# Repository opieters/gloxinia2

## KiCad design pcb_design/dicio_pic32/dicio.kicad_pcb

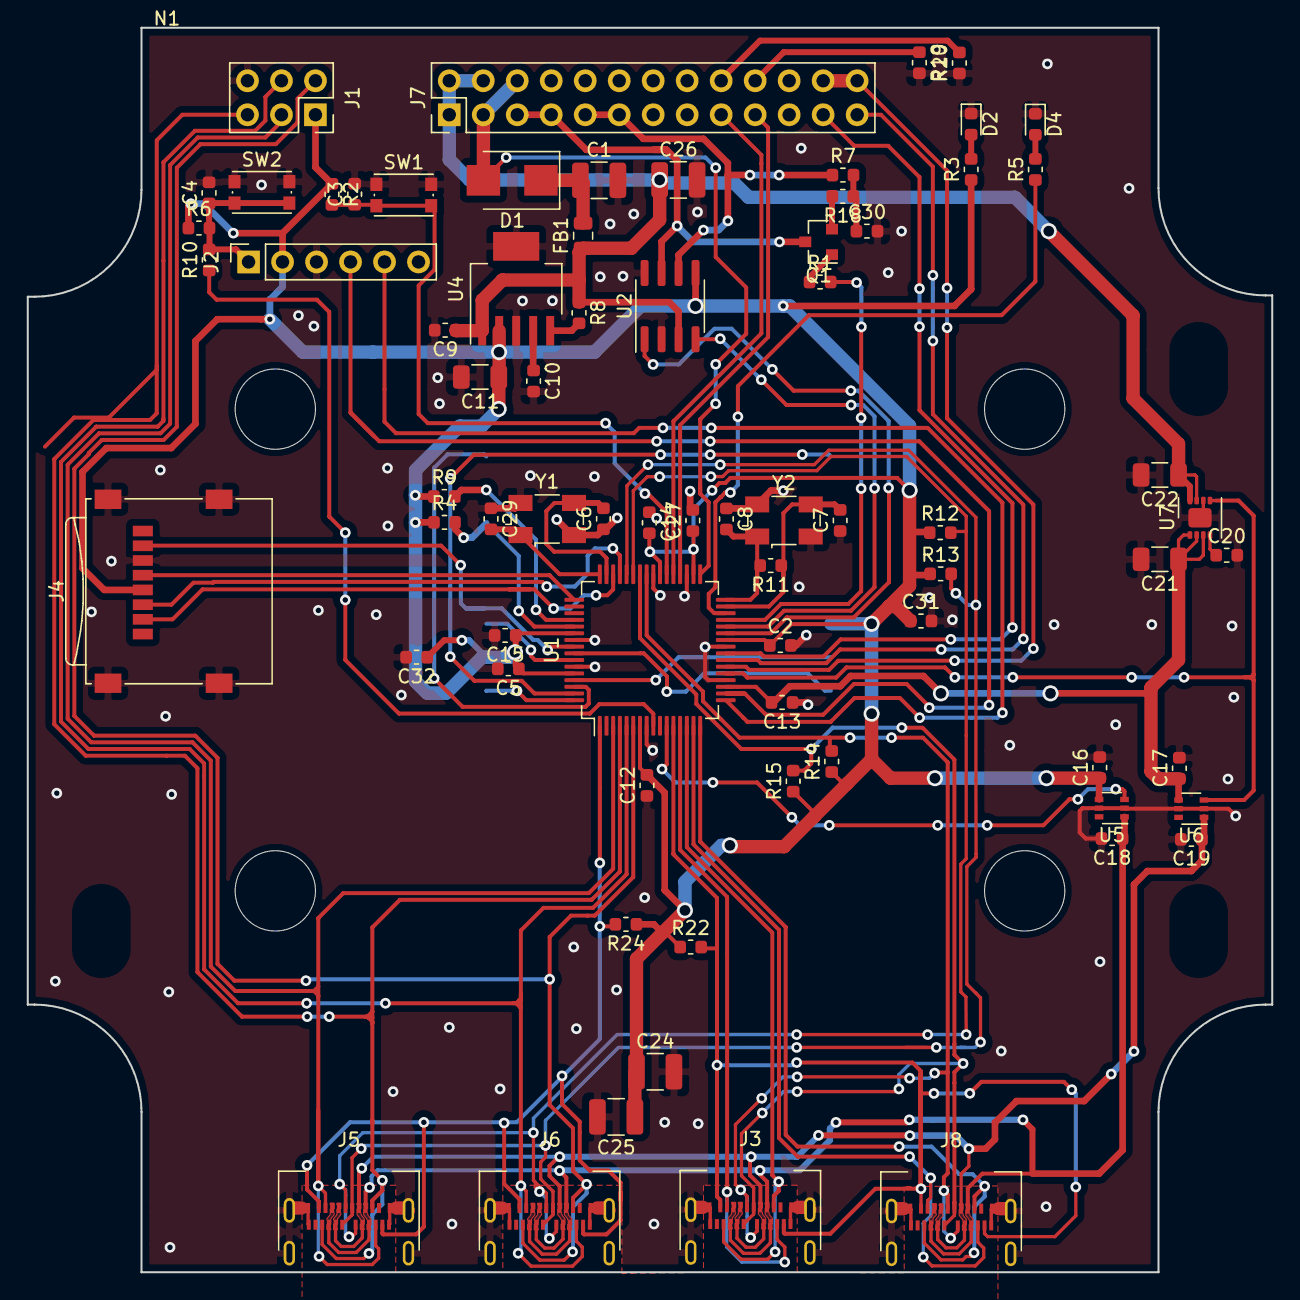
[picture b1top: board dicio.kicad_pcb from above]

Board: 2 copper layers, 93.0 x 93.0 mm, 75 parts (1 on the bottom side), 66 nets.

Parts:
C1, C24, C25, C26: 10uF; C_1210_3225Metric
C2, C5, C12, C13, C14, C15, C18, C19, C27, C31, C32: 0.1uF; C_0603_1608Metric
C3, C4: 0.01uF; C_0603_1608Metric
C6, C7, C8, C29: 20pF; C_0603_1608Metric
C9, C10, C16, C17: 1uF; C_0603_1608Metric
C11: 2.2uF; C_1206_3216Metric
C20: 1nF; C_0603_1608Metric
C21, C22: 4.7uF; C_1206_3216Metric
C30: 4.7nF; C_0603_1608Metric
D1: D_Schottky; D_SMB
D2, D4: LED; LED_0603_1608Metric
FB1: Ferrite_Bead; L_0805_2012Metric
J1: Conn_02x03_Counter_Clockwise; PinSocket_2x03_P2.54mm_Vertical
J2: Conn_01x06_Female; PinSocket_1x06_P2.54mm_Vertical
J3, J5, J6, J8: USB_C_Receptacle; USB_C_Receptacle_Amphenol_12401861XX12A
J4: Micro_SD_Card; microSD_HC_Wuerth_693072010801
J7: Conn_02x13_Odd_Even; PinHeader_2x13_P2.54mm_Vertical
N1: Housing; Enclosure-Gloxinia2
Q1: Q_NMOS_GSD; SOT-23
R1: 1k; R_0603_1608Metric
R2, R6, R8: 10k; R_0603_1608Metric
R3, R5: 750; R_0603_1608Metric
R4, R9: 100k; R_0603_1608Metric
R7, R18: 60R; R_0603_1608Metric
R10: 270R; R_0603_1608Metric
R11: 1M; R_0603_1608Metric
R12, R13, R14, R15, R22, R24: 4.9k; R_0603_1608Metric
R19, R20: 5.1k; R_0603_1608Metric
SW1, SW2: SW_SPST; SW_Push_1P1T_NO_CK_KMR2
U1: PIC32MZ0512EFF064; TQFP-64_10x10mm_P0.5mm
U2: MCP2542FD; SOIC-8_3.9x4.9mm_P1.27mm
U3: S70FL01GS; SOIC-16_25.75x18.75mm_P2.5mm
U4: TPS737; SOT-223-6
U5, U6: SiP32431; SOT-363_SC-70-6
U7: ADM7170; LFCSP-8-1EP_3x3mm_P0.5mm_EP1.45x1.74mm
Y1, Y2: Crystal_GND24; Crystal_SMD_Abracon_ABM3B-4Pin_5.0x3.2mm

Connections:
+3.3VA: C13.2, C17.1, C21.1, U1.19, U6.4, U7.1, U7.2, U7.3
+3V3: C2.1, C5.1, C11.1, C12.2, C14.2, C15.1, C16.1, C24.1, C25.1, C27.1, C31.1, C32.1, J1.1, J2.2, J4.4, R2.1, R3.1, R4.1, R6.1, R9.1, R12.1, R13.1, R14.1, R15.1, R22.1, R24.1, U1.7, U1.26, U1.34, U1.39, U1.54, U1.60, U2.5, U3.2, U3.14, U4.2, U5.4
/AS1: J8.A10, J8.B10, U1.16
/AS1-: J8.A3, J8.B3, U1.15
/AS2: J3.A10, J3.B10, U1.14
/AS2-: J3.A3, J3.B3, U1.13
/AS3: J1.5, J5.A10, J5.B10, U1.4
/AS3-: J1.3, J5.A3, J5.B3, U1.3
/AS4: J1.2, J6.A10, J6.B10, U1.6
/AS4-: J1.4, J6.A3, J6.B3, U1.5
/AS_PS: C19.1, J3.A5, J3.A8, J3.B5, J3.B8, J5.A5, J5.A8, J5.B5, J5.B8, J6.A5, J6.A8, J6.B5, J6.B8, J8.A5, J8.A8, J8.B5, J8.B8, U6.1
/AS_PS_SW: U1.21, U6.3, U7.5
/BTN: C3.1, R2.2, SW1.2, U1.38
/C1RX: U1.28, U2.4
/C1TX: U1.27, U2.1
/CAN_C1: J7.23, U1.24
/CAN_C2: J7.25, U1.23
/CAN_H: J7.5, J7.7, Q1.3, U2.7
/CAN_L: J7.9, J7.11, R7.1, U2.6
/CC1: J7.18, R20.2
/D+: J7.17, U1.37
/D-: J7.19, U1.36
/EN: R8.2, U4.5
/ERR: R5.1, U1.30
/MISO1: J4.7, U1.56
/MOSI1: J4.3, U1.45
/OSC1: C7.2, R11.1, U1.31, Y2.3
/OSC2: C8.2, R11.2, U1.32, Y2.1
/PGC: J2.5, U1.17
/PGD: J2.4, U1.18
/SCK1: J4.5, U1.49
/SCL1: J3.A7, J3.B7, J8.A7, J8.B7, R15.2, U1.42
/SCL2: J5.A7, J5.B7, J6.A7, J6.B7, R13.2, U1.44
/SDA1: J3.A6, J3.B6, J8.A6, J8.B6, R14.2, U1.41
/SDA2: J5.A6, J5.B6, J6.A6, J6.B6, R12.2, U1.43
/SOSC1: C6.2, U1.47, Y1.3
/SOSC2: C29.2, U1.48, Y1.1
/SQICLK: U1.57, U3.16
/SQID0: U1.61, U3.15
/SQID1: U1.62, U3.8
/SQID2: U1.63, U3.9
/SQID3: U1.64, U3.1
/SYNC: J7.24, J7.26, U1.22
/S_PS: C18.1, J3.A4, J3.A9, J3.B4, J3.B9, J5.A4, J5.A9, J5.B4, J5.B9, J6.A4, J6.A9, J6.B4, J6.B9, J8.A4, J8.A9, J8.B4, J8.B9, U5.1
/S_PS_SW: U1.11, U5.3
/TERM: R1.2, U1.29
/VCONN: J7.20, R19.1
/V_USBC: D1.2, J7.3, J7.6, U1.33
/~CS_SD: J4.2, U1.46
/~INT1: J3.A2, J3.B2, J8.A2, J8.B2, R22.2, U1.12
/~INT2: J5.A2, J5.B2, J6.A2, J6.B2, R24.2, U1.1
/~MCLR_w: R10.1, U1.9
/~MCLR: C4.1, J2.1, R6.2, R10.2, SW2.2
/~RESET_M: U1.58, U3.3
/~SQICS0: R9.2, U1.52, U3.7
/~SQICS1: R4.2, U1.53, U3.6
GND: C1.2, C2.2, C3.2, C4.2, C5.2, C6.1, C7.1, C8.1, C9.2, C10.2, C11.2, C12.1, C13.1, C14.1, C15.2, C16.2, C17.2, C18.2, C19.2, C20.2, C21.2, C22.2, C24.2, C25.2, C26.2, C27.2, C29.1, C30.2, C31.2, C32.2, D2.1, D4.1, J1.6, J2.3, J3.A1, J3.A12, J3.B1, J3.B12, J3.S1, J4.6, J4.9, J5.A1, J5.A12, J5.B1, J5.B12, J5.S1, J6.A1, J6.A12, J6.B1, J6.B12, J6.S1, J8.A1, J8.A12, J8.B1, J8.B12, J8.S1, R19.2, R20.1, SW1.1, SW2.1, U1.8, U1.20, U1.25, U1.35, U1.40, U1.55, U1.59, U2.2, U2.8, U3.10, U4.3, U4.6, U5.2, U5.5, U6.2, U6.5, U7.6, U7.9, Y1.2, Y1.4, Y2.2, Y2.4
unnamed: C1.1, D1.1, FB1.2
unnamed: C10.1, U4.4
unnamed: C20.1, U7.4
unnamed: C30.1, R7.2, R18.1
unnamed: D2.2, R3.2
unnamed: D4.2, R5.2
unnamed: Q1.1, R1.1
unnamed: Q1.2, R18.2
VBUS: C9.1, C22.1, C26.1, FB1.1, J7.1, J7.2, J7.4, R8.1, U2.3, U4.1, U7.7, U7.8

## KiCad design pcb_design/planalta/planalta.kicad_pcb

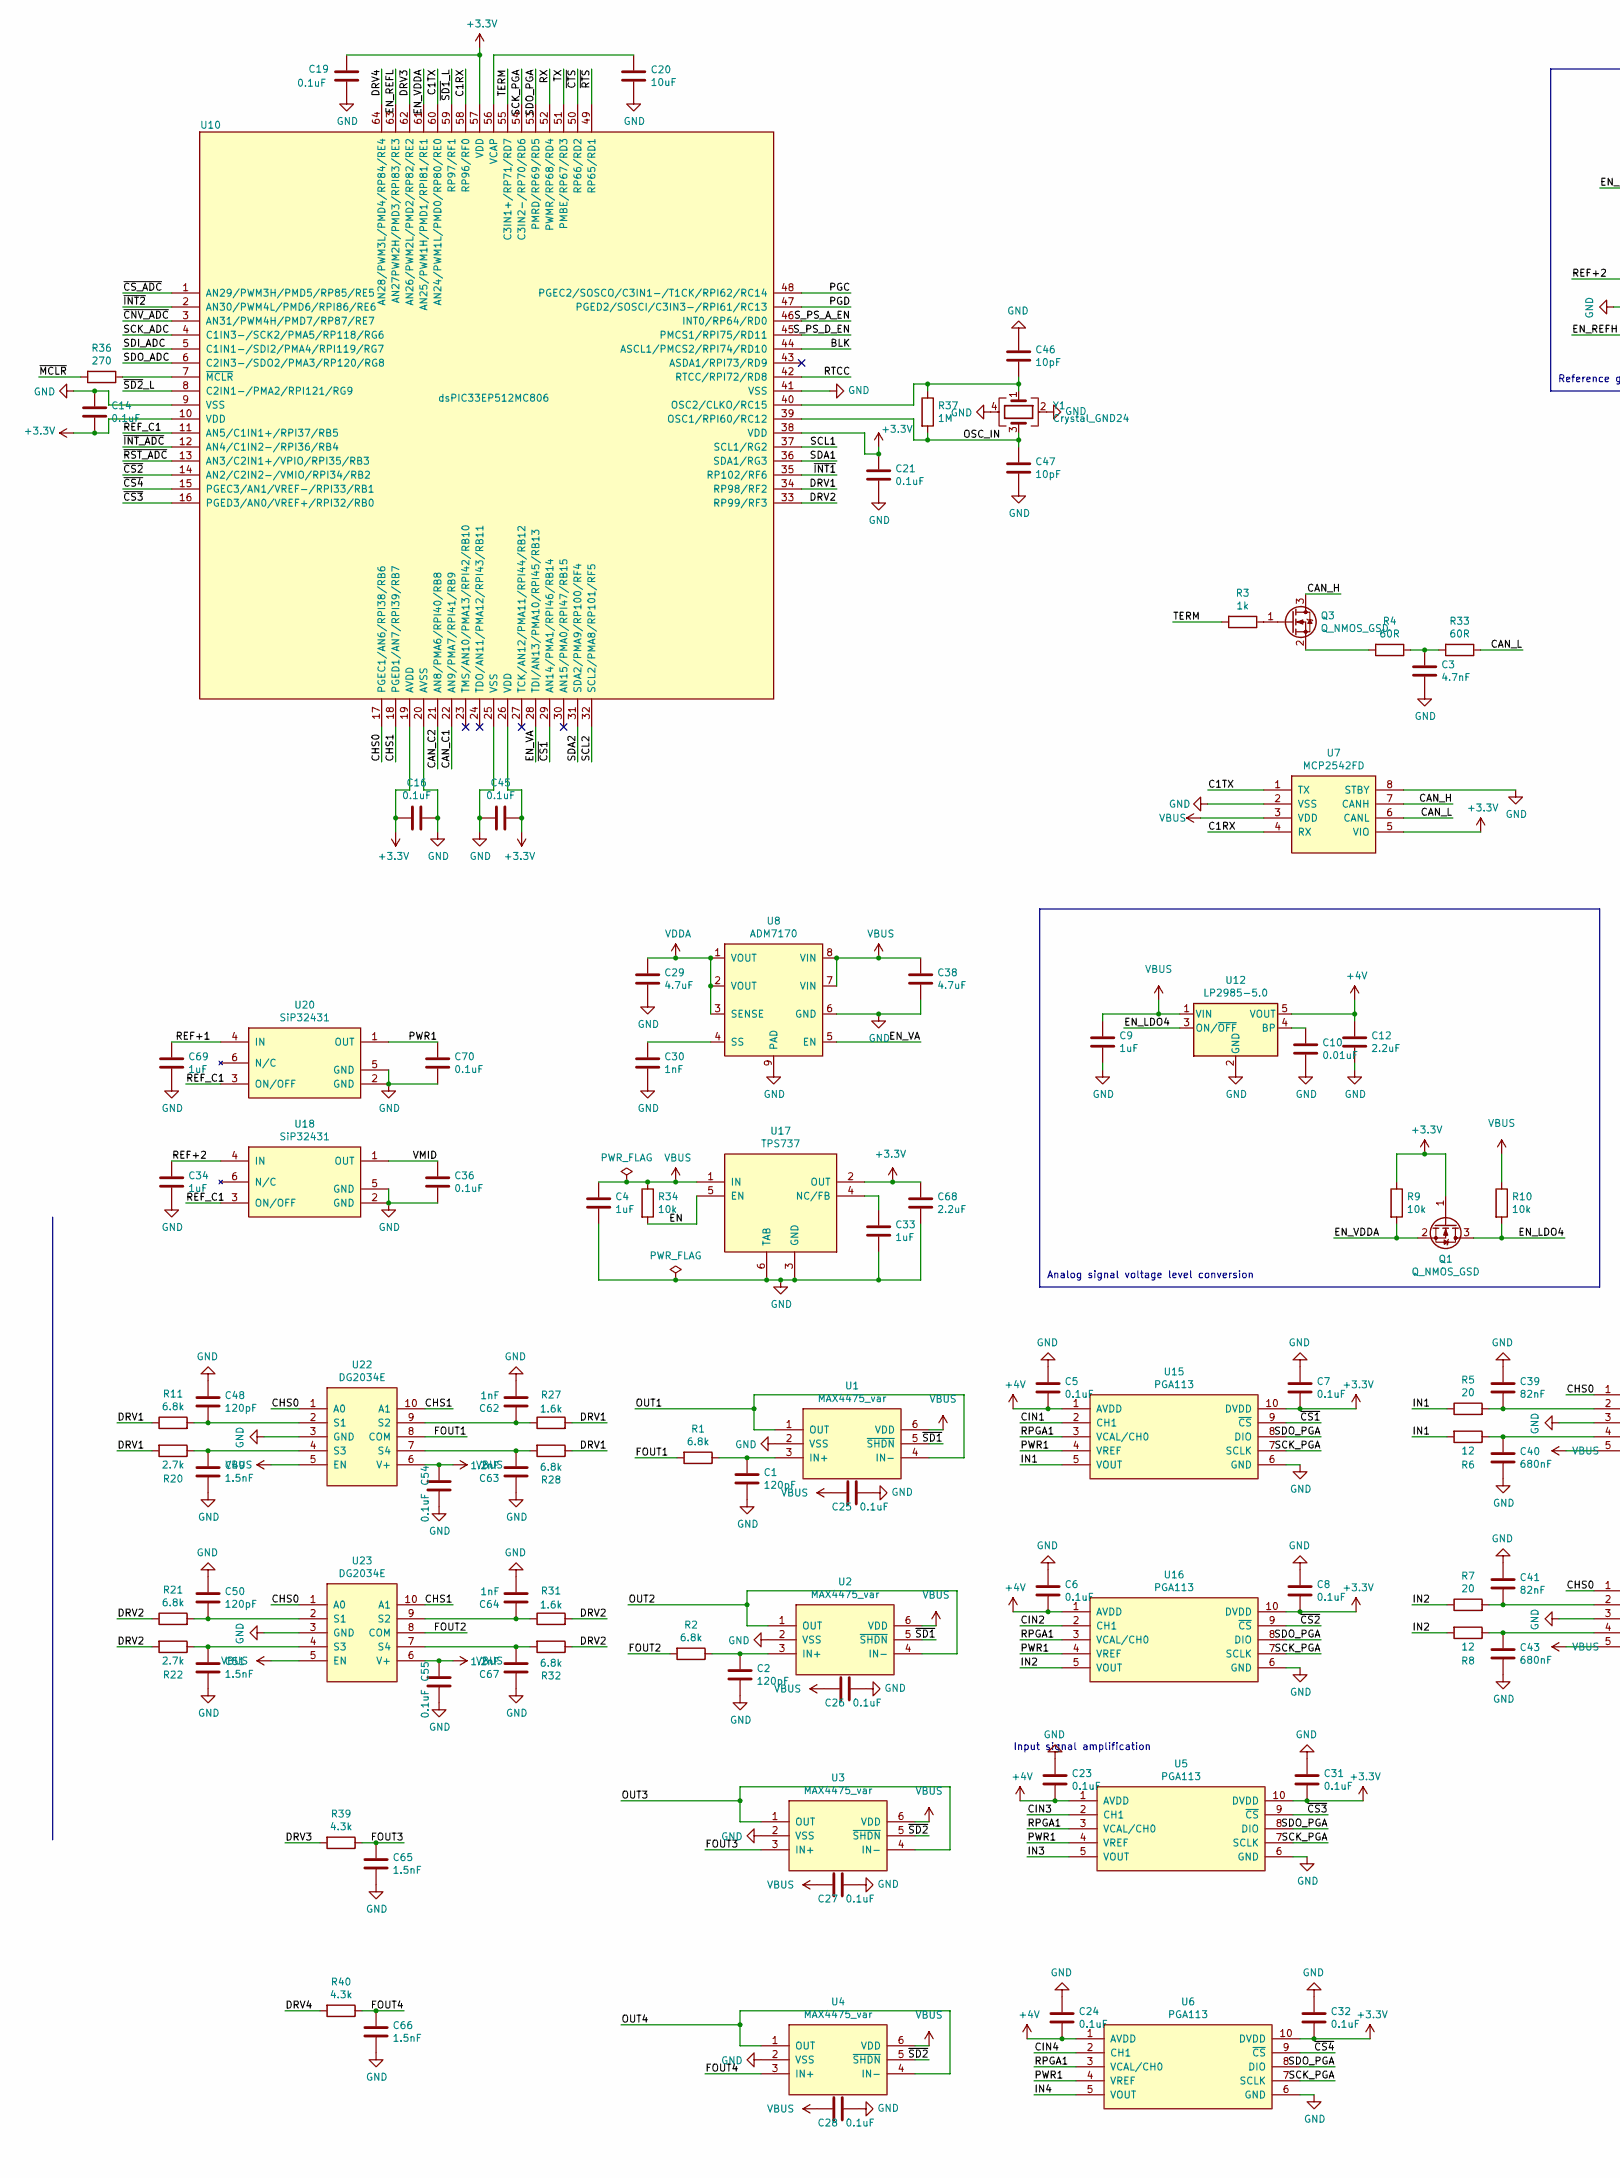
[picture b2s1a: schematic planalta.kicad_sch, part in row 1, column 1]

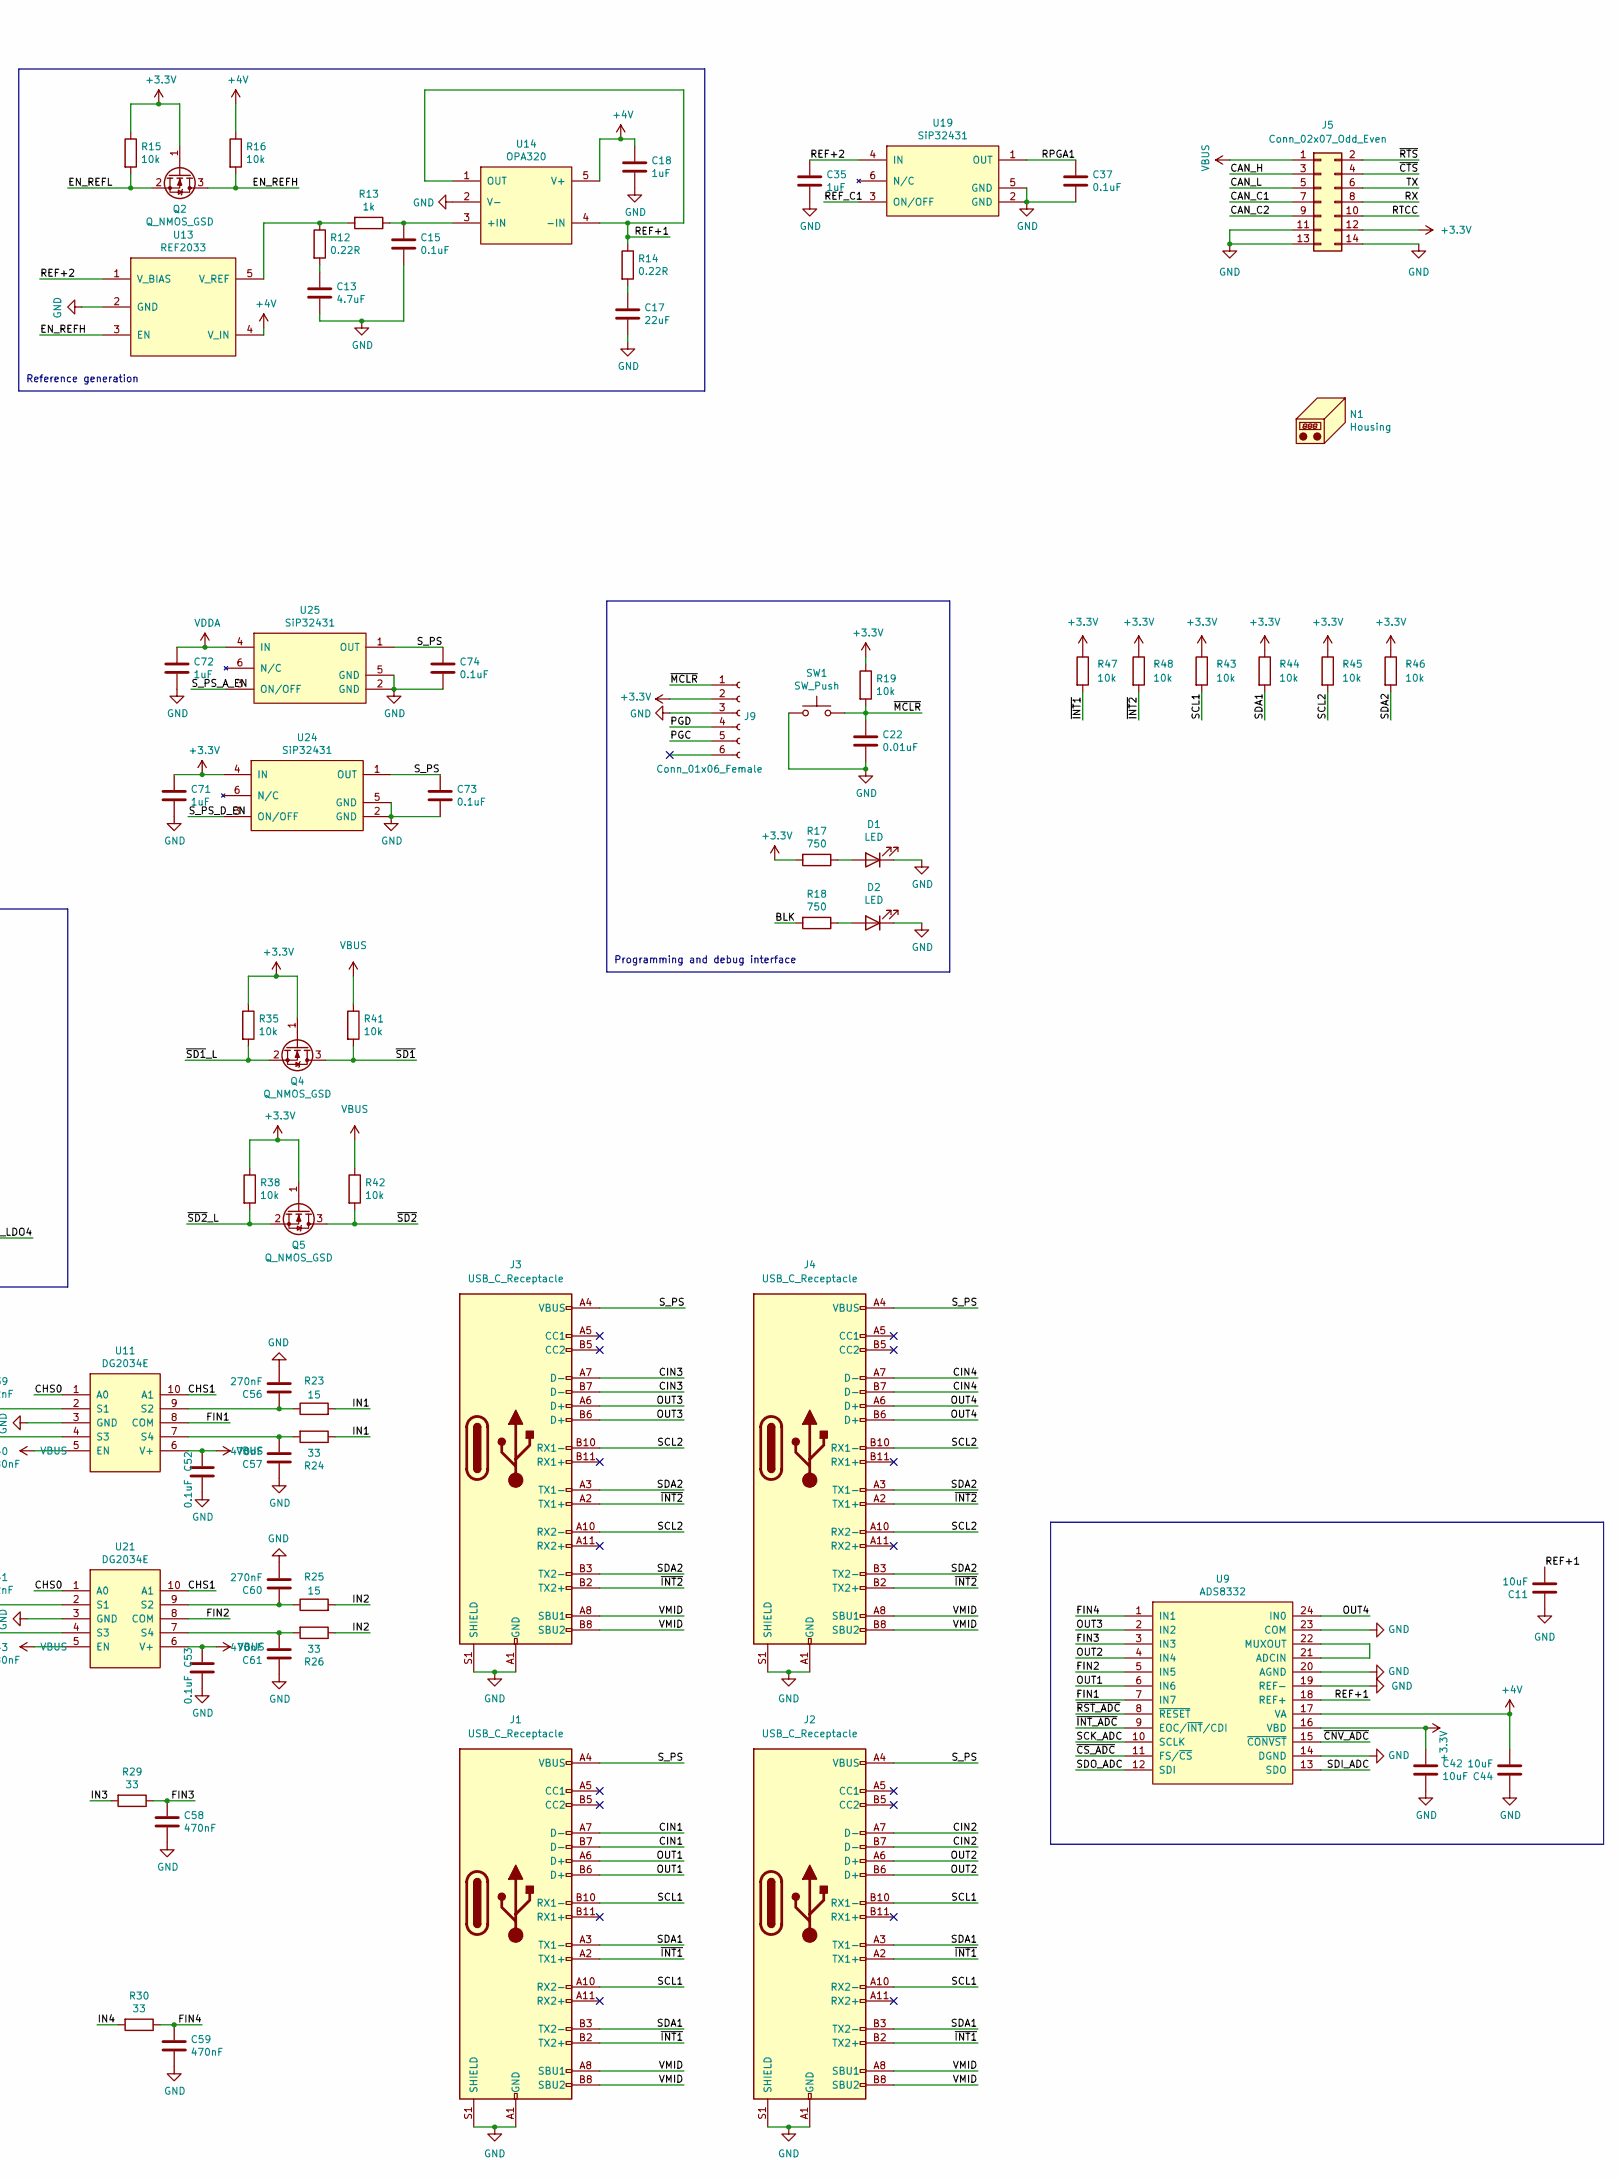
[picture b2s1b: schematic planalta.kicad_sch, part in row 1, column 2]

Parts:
C1, C2, C48, C50: 120pF; C_0603_1608Metric; Mouser 80-C0603C121J5GAC
C3: 4.7nF; C_0603_1608Metric
C4, C33: 1uF; C_0603_1608Metric; Mouser 963-TMK325B7105KD-T
C5, C6, C7, C8, C14, C15, C16, C19, C21, C23, C24, C25, C26, C27, C28, C31, C32, C36, C37, C45, C52, C53, C54, C55, C70, C73, C74: 0.1uF; C_0603_1608Metric; Mouser 710-885012206071
C9, C18, C34, C35, C69, C71, C72: 1uF; C_0603_1608Metric; Mouser 81-GCM188R71C105K64D
C10, C22: 0.01uF; C_0603_1608Metric; Mouser 81-GRM033C81E103KE4E
C11, C20, C42, C44: 10uF; C_1210_3225Metric; Mouser 963-TMK325BJ106KM-P
C12, C68: 2.2uF; C_1206_3216Metric; Mouser 791-1206X225K250CT
C13: 4.7uF; C_1206_3216Metric; Mouser 81-GCG31CR71E475JA1L
C17: 22uF; C_1206_3216Metric; Mouser 963-TMK316BBJ226ML-T
C29, C38: 4.7uF; C_1206_3216Metric
C30: 1nF; C_0603_1608Metric
C39, C41: 82nF; C_0603_1608Metric; Mouser 80-C0603C823J3R
C40, C43: 680nF; C_0603_1608Metric; Mouser 710-885012206051
C46, C47: 10pF; C_0603_1608Metric; Mouser 603-CC603FRNPO9BN100
C49, C51, C65, C66: 1.5nF; C_0603_1608Metric; Mouser 710-885012206035
C56, C60: 270nF; C_0603_1608Metric; Mouser 80-C0603C274K8P
C57, C58, C59, C61: 470nF; C_0603_1608Metric; Mouser 710-885012206075
C62, C64: 1nF; C_0603_1608Metric; Mouser 963-TMK325B7105KD-T
C63, C67: 1.2nF; C_0603_1608Metric; Mouser 81-GRM1885C1H122JA01
D1, D2: LED; LED_0603_1608Metric; Mouser 78-TLMS1000
J1, J2, J3, J4: USB_C_Receptacle; USB_C_Receptacle_Amphenol_12401861XX12A
J5: Conn_02x07_Odd_Even; SAMTEC_TMMH-107-01-T-DV
J9: Conn_01x06_Female; PinSocket_1x06_P2.54mm_Vertical
N1: Housing; Enclosure-Gloxinia4; Mouser 546-1554LA2GYCL
Q1, Q2, Q4, Q5: Q_NMOS_GSD; SOT-23; Mouser 512-BSS138
Q3: Q_NMOS_GSD; SOT-23; Mouser 771-PMV20XNER
R1, R2, R11, R21, R28, R32: 6.8k; R_0603_1608Metric; Mouser 667-ERJ-3RBD6801V
R3: 1k; R_0603_1608Metric
R4, R33: 60R; R_0603_1608Metric; Mouser 594-5063JD120R0F
R5, R7: 20; R_0603_1608Metric; Mouser 71-CRCW060320R0FKEAC
R6, R8: 12; R_0603_1608Metric; Mouser 667-ERJ-3EKF15R0V
R9, R10, R15, R16, R19, R34, R35, R38, R41, R42: 10k; R_0603_1608Metric; Mouser 284-APC0603B10K0N
R12, R14: 0.22R; R_0603_1608Metric; Mouser 667-ERJ-3RQFR22V
R13: 1k; R_0603_1608Metric; Mouser 652-CR0603-FX1001HLF
R17, R18: 750; R_0603_1608Metric; Mouser 603-RC0603FR-07750RL
R20, R22: 2.7k; R_0603_1608Metric; Mouser 603-AC0603FR-102K7L
R23, R25: 15; R_0603_1608Metric; Mouser 667-ERJ-3EKF15R0V
R24, R26, R29, R30: 33; R_0603_1608Metric; Mouser 71-CRCW060333R0FKEAC
R27, R31: 1.6k; R_0603_1608Metric; Mouser 603-RC0603FR-071K6L
R36: 270; R_0603_1608Metric; Mouser 603-RC0603FR-07270RL
R37: 1M; R_0603_1608Metric; Mouser 603-RC0603FR-101ML
R39, R40: 4.3k; R_0603_1608Metric
R43, R44, R45, R46, R47, R48: 10k; R_0603_1608Metric
SW1: SW_Push; SW_SPST_KMR2; Mouser 611-KMR621NGLFS
U1, U2, U3, U4: MAX4475_var; SOT-23-6; Mouser 700-MAX4475AUT+T
U5, U6, U15, U16: PGA113; MSOP-10_3x3mm_P0.5mm; Mouser 595-PGA113AIDGSR
U7: MCP2542FD; SOIC-8_3.9x4.9mm_P1.27mm; Mouser 579-MCP2542FDT-E/SN
U8: ADM7170; LFCSP-8-1EP_3x3mm_P0.5mm_EP1.45x1.74mm
U9: ADS8332; TSSOP-24_4.4x7.8mm_P0.65mm; Mouser 595-ADS8332IBPWR
U10: dsPIC33EP512MC806; TQFP-64_10x10mm_P0.5mm; Mouser 579-33EP512MC806IPT
U11, U21, U22, U23: DG2034E; MSOP-10_3x3mm_P0.5mm; Mouser 78-DG2034EDQ-T1-GE3
U12: LP2985-5.0; SOT-23-5; Mouser 926-LP2985IM540NOPB
U13: REF2033; SOT-23-5; Mouser 595-REF2033AIDDCR
U14: OPA320; SOT-23-5; Mouser 595-OPA320AIDBVR
U17: TPS737; SOT-223-6; Mouser 595-TPS73733DCQR
U18, U19, U20, U24, U25: SiP32431; SOT-363_SC-70-6; Mouser 781-SIP32431DR3-GE3
Y1: Crystal_GND24; Crystal_SMD_Abracon_ABM3B-4Pin_5.0x3.2mm; Mouser 520-80-10-30B-CWNT

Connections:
+3.3V: C7.2, C8.2, C14.2, C16.2, C19.1, C21.1, C31.2, C32.2, C42.1, C45.1, C68.1, C71.1, J5.12, J9.2, Q1.1 (G), Q2.1 (G), Q4.1 (G), Q5.1 (G), R9.1, R15.1, R17.2, R19.1, R35.1, R38.1, R43.1, R44.1, R45.1, R46.1, R47.1, R48.1, U5.10 (DVDD), U6.10 (DVDD), U7.5 (VIO), U9.16 (VBD), U10.10 (VDD), U10.19 (AVDD), U10.26 (VDD), U10.38 (VDD), U10.57 (VDD), U15.10 (DVDD), U16.10 (DVDD), U17.2 (OUT), U24.4 (IN)
+4V: C5.2, C6.2, C12.1, C18.1, C23.2, C24.2, C44.2, R16.1, U5.1 (AVDD), U6.1 (AVDD), U9.17 (VA), U12.5 (VOUT), U13.4 (V_IN), U14.5 (V+), U15.1 (AVDD), U16.1 (AVDD)
/BLK: R18.2, U10.44 (ASCL1/PMCS2/RPI74/RD10)
/C1RX: U7.4 (RX), U10.58 (RP96/RF0)
/C1TX: U7.1 (TX), U10.60 (AN24/PWM1L/PMD0/RP80/RE0)
/CAN_C1: J5.7, U10.22 (AN9/PMA7/RPI41/RB9)
/CAN_C2: J5.9, U10.21 (AN8/PMA6/RPI40/RB8)
/CAN_H: J5.3, Q3.3 (D), U7.7 (CANH)
/CAN_L: J5.5, R33.1, U7.6 (CANL)
/CHS0: U10.17 (PGEC1/AN6/RPI38/RB6), U11.1 (A0), U21.1 (A0), U22.1 (A0), U23.1 (A0)
/CHS1: U10.18 (PGED1/AN7/RPI39/RB7), U11.10 (A1), U21.10 (A1), U22.10 (A1), U23.10 (A1)
/CIN1: J1.A7 (D-), J1.B7 (D-), U15.2 (CH1)
/CIN2: J2.A7 (D-), J2.B7 (D-), U16.2 (CH1)
/CIN3: J3.A7 (D-), J3.B7 (D-), U5.2 (CH1)
/CIN4: J4.A7 (D-), J4.B7 (D-), U6.2 (CH1)
/DRV1: R11.1, R20.2, R27.2, R28.1, U10.34 (RP98/RF2)
/DRV2: R21.1, R22.2, R31.2, R32.1, U10.33 (RP99/RF3)
/DRV3: R39.2, U10.62 (AN26/PWM2L/PMD2/RP82/RE2)
/DRV4: R40.2, U10.64 (AN28/PWM3L/PMD4/RP84/RE4)
/EN: R34.2, U17.5 (EN)
/EN_LDO4: Q1.3 (D), R10.2, U12.3 (ON/~OFF)
/EN_REFH: Q2.3 (D), R16.2, U13.3 (EN)
/EN_REFL: Q2.2 (S), R15.2, U10.63 (AN27PWM2H/PMD3/RPI83/RE3)
/EN_VA: U8.5 (EN), U10.28 (TDI/AN13/PMA10/RPI45/RB13)
/EN_VDDA: Q1.2 (S), R9.2, U10.61 (AN25/PWM1H/PMD1/RPI81/RE1)
/FIN1: U9.7 (IN7), U11.8 (COM)
/FIN2: U9.5 (IN5), U21.8 (COM)
/FIN3: C58.1, R29.1, U9.3 (IN3)
/FIN4: C59.1, R30.1, U9.1 (IN1)
/FOUT1: R1.2, U22.8 (COM)
/FOUT2: R2.2, U23.8 (COM)
/FOUT3: C65.1, R39.1, U3.3 (IN+)
/FOUT4: C66.1, R40.1, U4.3 (IN+)
/IN1: R5.1, R6.2, R23.2, R24.1, U15.5 (VOUT)
/IN2: R7.1, R8.2, R25.2, R26.1, U16.5 (VOUT)
/IN3: R29.2, U5.5 (VOUT)
/IN4: R30.2, U6.5 (VOUT)
/OSC_IN: C47.1, R37.2, U10.39 (OSC1/RPI60/RC12), Y1.3
/OUT1: J1.A6 (D+), J1.B6 (D+), U1.1 (OUT), U1.4 (IN-), U9.6 (IN6)
/OUT2: J2.A6 (D+), J2.B6 (D+), U2.1 (OUT), U2.4 (IN-), U9.4 (IN4)
/OUT3: J3.A6 (D+), J3.B6 (D+), U3.1 (OUT), U3.4 (IN-), U9.2 (IN2)
/OUT4: J4.A6 (D+), J4.B6 (D+), U4.1 (OUT), U4.4 (IN-), U9.24 (IN0)
/PGC: J9.5, U10.48 (PGEC2/SOSCO/C3IN1-/T1CK/RPI62/RC14)
/PGD: J9.4, U10.47 (PGED2/SOSCI/C3IN3-/RPI61/RC13)
/PWR1: C70.1, U5.4 (VREF), U6.4 (VREF), U15.4 (VREF), U16.4 (VREF), U20.1 (OUT)
/REF+1: C11.2, C69.1, R14.1, U9.18 (REF+), U14.1 (OUT), U14.4 (-IN), U20.4 (IN)
/REF+2: C34.1, C35.1, U13.1 (V_BIAS), U18.4 (IN), U19.4 (IN)
/REF_C1: U10.11 (AN5/C1IN1+/RPI37/RB5), U18.3 (ON/OFF), U19.3 (ON/OFF), U20.3 (ON/OFF)
/RPGA1: C37.1, U5.3 (VCAL/CH0), U6.3 (VCAL/CH0), U15.3 (VCAL/CH0), U16.3 (VCAL/CH0), U19.1 (OUT)
/RTCC: J5.10, U10.42 (RTCC/RPI72/RD8)
/RX: J5.8, U10.52 (PWMR/RP68/RD4)
/SCK_ADC: U9.10 (SCLK), U10.4 (C1IN3-/SCK2/PMA5/RP118/RG6)
/SCK_PGA: U5.7 (SCLK), U6.7 (SCLK), U10.54 (C3IN2-/RP70/RD6), U15.7 (SCLK), U16.7 (SCLK)
/SCL1: J1.A10 (RX2-), J1.B10 (RX1-), J2.A10 (RX2-), J2.B10 (RX1-), R43.2, U10.37 (SCL1/RG2)
/SCL2: J3.A10 (RX2-), J3.B10 (RX1-), J4.A10 (RX2-), J4.B10 (RX1-), R45.2, U10.32 (SCL2/PMA8/RP101/RF5)
/SDA1: J1.A3 (TX1-), J1.B3 (TX2-), J2.A3 (TX1-), J2.B3 (TX2-), R44.2, U10.36 (SDA1/RG3)
/SDA2: J3.A3 (TX1-), J3.B3 (TX2-), J4.A3 (TX1-), J4.B3 (TX2-), R46.2, U10.31 (SDA2/PMA9/RP100/RF4)
/SDI_ADC: U9.13 (SDO), U10.5 (C1IN1-/SDI2/PMA4/RPI119/RG7)
/SDO_ADC: U9.12 (SDI), U10.6 (C2IN3-/SDO2/PMA3/RP120/RG8)
/SDO_PGA: U5.8 (DIO), U6.8 (DIO), U10.53 (PMRD/RP69/RD5), U15.8 (DIO), U16.8 (DIO)
/S_PS: C73.1, C74.1, J1.A4 (VBUS), J1.A9 (VBUS), J1.B4 (VBUS), J1.B9 (VBUS), J2.A4 (VBUS), J2.A9 (VBUS), J2.B4 (VBUS), J2.B9 (VBUS), J3.A4 (VBUS), J3.A9 (VBUS), J3.B4 (VBUS), J3.B9 (VBUS), J4.A4 (VBUS), J4.A9 (VBUS), J4.B4 (VBUS), J4.B9 (VBUS), U24.1 (OUT), U25.1 (OUT)
/S_PS_A_EN: U10.46 (INT0/RP64/RD0), U25.3 (ON/OFF)
/S_PS_D_EN: U10.45 (PMCS1/RPI75/RD11), U24.3 (ON/OFF)
/TERM: R3.2, U10.55 (C3IN1+/RP71/RD7)
/TX: J5.6, U10.51 (PMBE/RP67/RD3)
/VMID: C36.1, J1.A8 (SBU1), J1.B8 (SBU2), J2.A8 (SBU1), J2.B8 (SBU2), J3.A8 (SBU1), J3.B8 (SBU2), J4.A8 (SBU1), J4.B8 (SBU2), U18.1 (OUT)
/~CNV_ADC: U9.15 (~CONVST), U10.3 (AN31/PWM4H/PMD7/RP87/RE7)
/~CS1: U10.29 (AN14/PMA1/RPI46/RB14), U15.9 (~CS)
/~CS2: U10.14 (AN2/C2IN2-/VMIO/RPI34/RB2), U16.9 (~CS)
/~CS3: U5.9 (~CS), U10.16 (PGED3/AN0/VREF+/RPI32/RB0)
/~CS4: U6.9 (~CS), U10.15 (PGEC3/AN1/VREF-/RPI33/RB1)
/~CS_ADC: U9.11 (FS/~CS), U10.1 (AN29/PWM3H/PMD5/RP85/RE5)
/~CTS: J5.4, U10.50 (RP66/RD2)
/~INT1: J1.A2 (TX1+), J1.B2 (TX2+), J2.A2 (TX1+), J2.B2 (TX2+), R47.2, U10.35 (RP102/RF6)
/~INT2: J3.A2 (TX1+), J3.B2 (TX2+), J4.A2 (TX1+), J4.B2 (TX2+), R48.2, U10.2 (AN30/PWM4L/PMD6/RPI86/RE6)
/~INT_ADC: U9.9 (EOC/~INT/CDI), U10.12 (AN4/C1IN2-/RPI36/RB4)
/~MCLR: C22.1, J9.1, R19.2, R36.2, SW1.2
/~RST_ADC: U9.8 (~RESET), U10.13 (AN3/C2IN1+/VPIO/RPI35/RB3)
/~RTS: J5.2, U10.49 (RP65/RD1)
/~SD1: Q4.3 (D), R41.2, U1.5 (~SHDN), U2.5 (~SHDN)
/~SD1_L: Q4.2 (S), R35.2, U10.59 (RP97/RF1)
/~SD2: Q5.3 (D), R42.2, U3.5 (~SHDN), U4.5 (~SHDN)
/~SD2_L: Q5.2 (S), R38.2, U10.8 (C2IN1-/PMA2/RPI121/RG9)
GND: C1.2, C2.2, C3.2, C4.2, C5.1, C6.1, C7.1, C8.1, C9.2, C10.2, C11.1, C12.2, C13.2, C14.1, C15.2, C16.1, C17.2, C18.2, C19.2, C20.2, C21.2, C22.2, C23.1, C24.1, C25.1, C26.1, C27.1, C28.1, C29.2, C30.2, C31.1, C32.1, C33.2, C34.2, C35.2, C36.2, C37.2, C38.2, C39.1, C40.2, C41.1, C42.2, C43.2, C44.1, C45.2, C46.1, C47.2, C48.1, C49.2, C50.1, C51.2, C52.1, C53.1, C54.1, C55.1, C56.2, C57.1, C58.2, C59.2, C60.2, C61.1, C62.2, C63.1, C64.2, C65.2, C66.2, C67.1, C68.2, C69.2, C70.2, C71.2, C72.2, C73.2, C74.2, D1.1 (K), D2.1 (K), J1.A1 (GND), J1.A12 (GND), J1.B1 (GND), J1.B12 (GND), J1.S1 (SHIELD), J2.A1 (GND), J2.A12 (GND), J2.B1 (GND), J2.B12 (GND), J2.S1 (SHIELD), J3.A1 (GND), J3.A12 (GND), J3.B1 (GND), J3.B12 (GND), J3.S1 (SHIELD), J4.A1 (GND), J4.A12 (GND), J4.B1 (GND), J4.B12 (GND), J4.S1 (SHIELD), J5.11, J5.13, J5.14, J9.3, SW1.1, U1.2 (VSS), U2.2 (VSS), U3.2 (VSS), U4.2 (VSS), U5.6 (GND), U6.6 (GND), U7.2 (VSS), U7.8 (STBY), U8.6 (GND), U8.9 (PAD), U9.14 (DGND), U9.19 (REF-), U9.20 (AGND), U9.23 (COM), U10.9 (VSS), U10.20 (AVSS), U10.25 (VSS), U10.41 (VSS), U11.3 (GND), U12.2 (GND), U13.2 (GND), U14.2 (V-), U15.6 (GND), U16.6 (GND), U17.3 (GND), U17.6 (TAB), U18.2 (GND), U18.5 (GND), U19.2 (GND), U19.5 (GND), U20.2 (GND), U20.5 (GND), U21.3 (GND), U22.3 (GND), U23.3 (GND), U24.2 (GND), U24.5 (GND), U25.2 (GND), U25.5 (GND), Y1.2, Y1.4
unnamed: C1.1, R1.1, U1.3 (IN+)
unnamed: C2.1, R2.1, U2.3 (IN+)
unnamed: C3.1, R4.1, R33.2
unnamed: C10.1, U12.4 (BP)
unnamed: C13.1, R12.2
unnamed: C15.1, R13.1, U14.3 (+IN)
unnamed: C17.1, R14.2
unnamed: C20.1, U10.56 (VCAP)
unnamed: C30.1, U8.4 (SS)
unnamed: C33.1, U17.4 (NC/FB)
unnamed: C39.2, R5.2, U11.2 (S1)
unnamed: C40.1, R6.1, U11.4 (S3)
unnamed: C41.2, R7.2, U21.2 (S1)
unnamed: C43.1, R8.1, U21.4 (S3)
unnamed: C46.2, R37.1, U10.40 (OSC2/CLKO/RC15), Y1.1
unnamed: C48.2, R11.2, U22.2 (S1)
unnamed: C49.1, R20.1, U22.4 (S3)
unnamed: C50.2, R21.2, U23.2 (S1)
unnamed: C51.1, R22.1, U23.4 (S3)
unnamed: C56.1, R23.1, U11.9 (S2)
unnamed: C57.2, R24.2, U11.7 (S4)
unnamed: C60.1, R25.1, U21.9 (S2)
unnamed: C61.2, R26.2, U21.7 (S4)
unnamed: C62.1, R27.1, U22.9 (S2)
unnamed: C63.2, R28.2, U22.7 (S4)
unnamed: C64.1, R31.1, U23.9 (S2)
unnamed: C67.2, R32.2, U23.7 (S4)
unnamed: D1.2 (A), R17.1
unnamed: D2.2 (A), R18.1
unnamed: Q3.1 (G), R3.1
unnamed: Q3.2 (S), R4.2
unnamed: R12.1, R13.2, U13.5 (V_REF)
unnamed: R36.1, U10.7 (~MCLR)
unnamed: U9.21 (ADCIN), U9.22 (MUXOUT)
VBUS: C4.1, C9.1, C25.2, C26.2, C27.2, C28.2, C38.1, C52.2, C53.2, C54.2, C55.2, J5.1, R10.1, R34.1, R41.1, R42.1, U1.6 (VDD), U2.6 (VDD), U3.6 (VDD), U4.6 (VDD), U7.3 (VDD), U8.7 (VIN), U8.8 (VIN), U11.5 (EN), U11.6 (V+), U12.1 (VIN), U17.1 (IN), U21.5 (EN), U21.6 (V+), U22.5 (EN), U22.6 (V+), U23.5 (EN), U23.6 (V+)
VDDA: C29.1, C72.1, U8.1 (VOUT), U8.2 (VOUT), U8.3 (SENSE), U25.4 (IN)

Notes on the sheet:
Reference generation
Analog signal voltage level conversion
Programming and debug interface
Input signal amplification

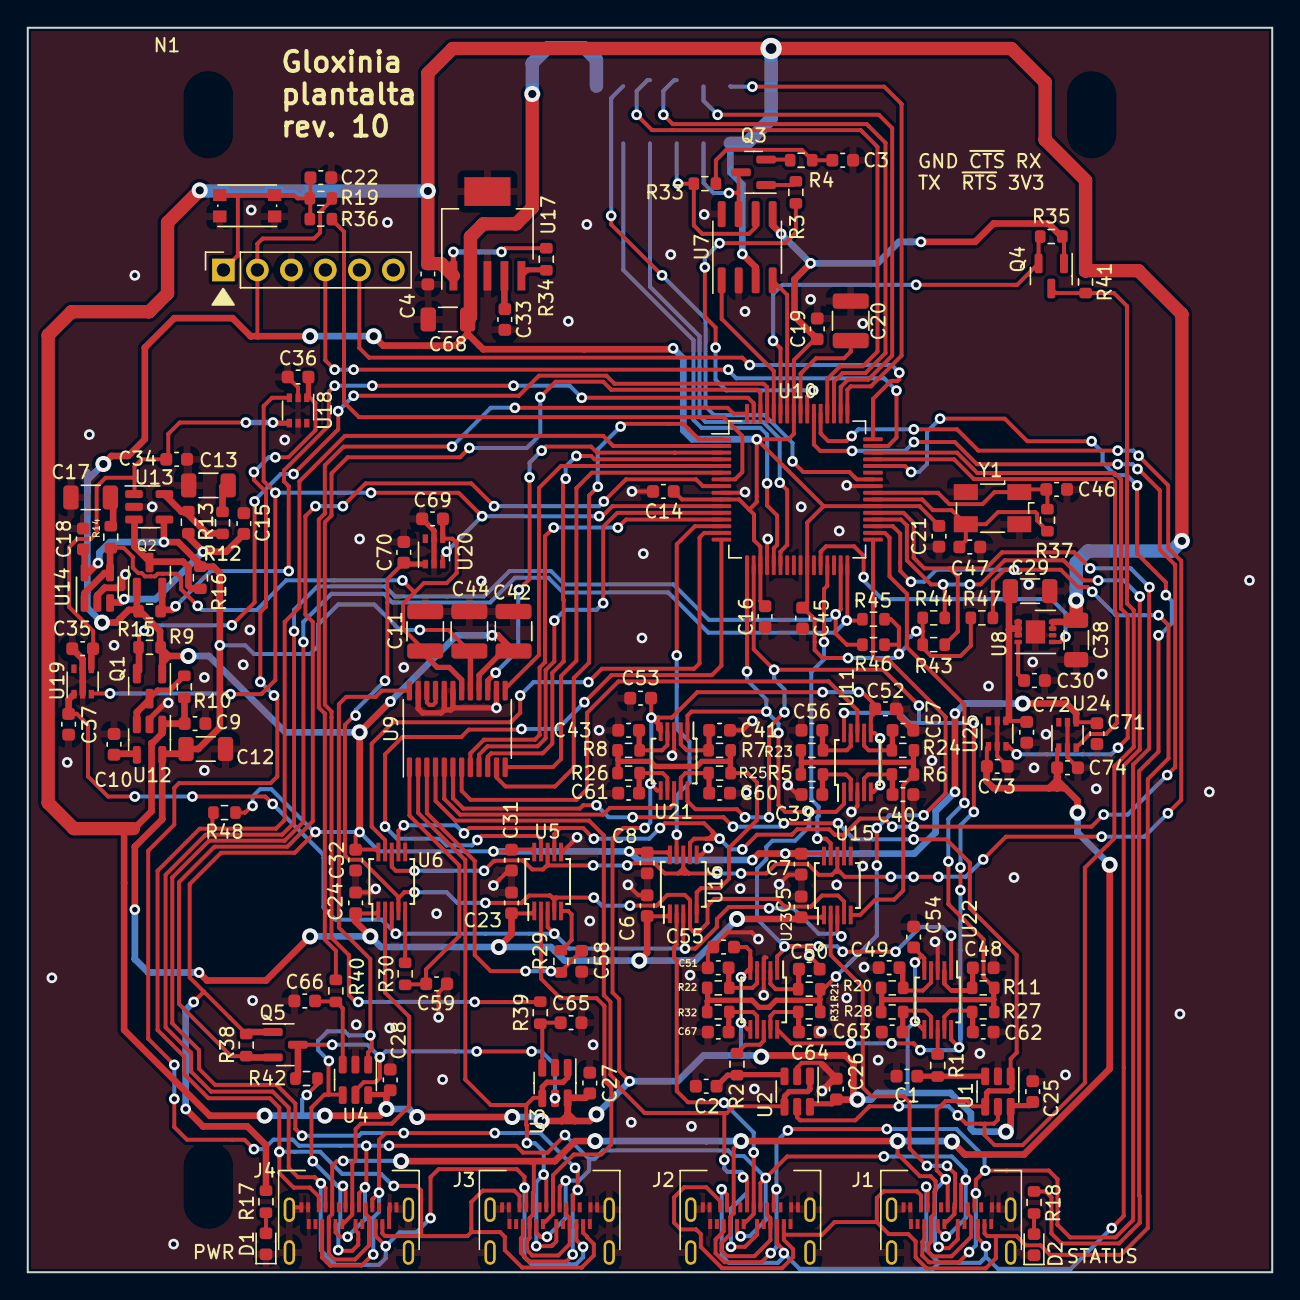
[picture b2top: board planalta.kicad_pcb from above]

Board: 2 copper layers, 93.0 x 93.0 mm, 163 parts (1 on the bottom side), 120 nets.

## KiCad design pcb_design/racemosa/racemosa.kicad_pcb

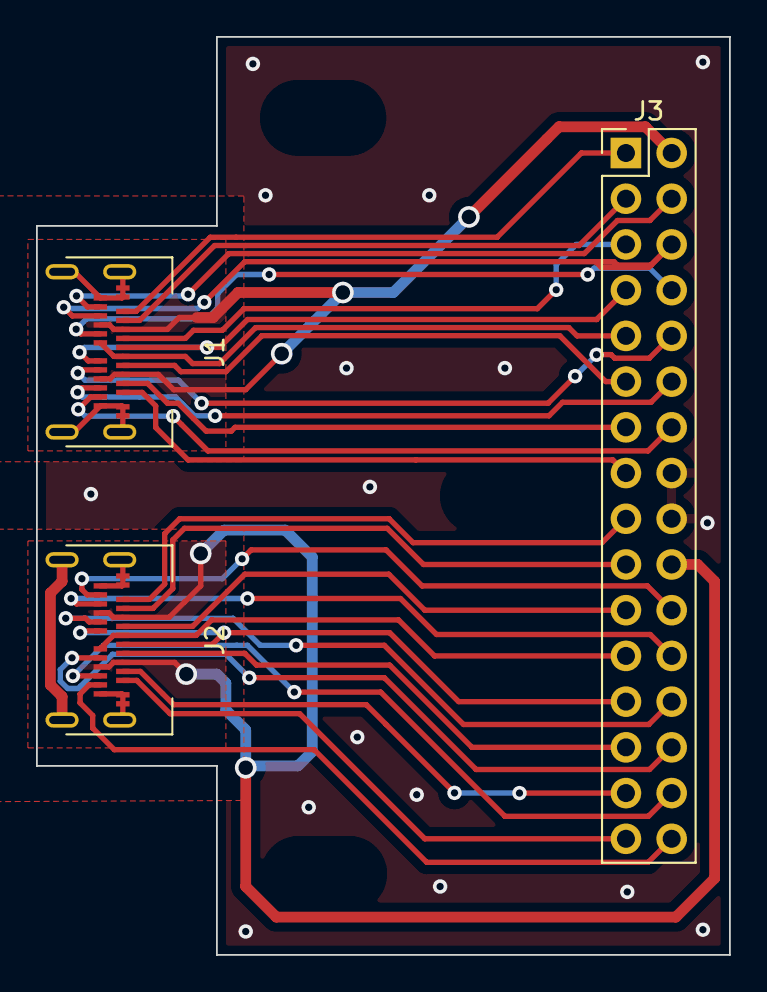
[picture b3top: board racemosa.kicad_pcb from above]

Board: 2 copper layers, 38.5 x 51.0 mm, 4 parts (0 on the bottom side), 31 nets.

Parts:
J1, J2: USB_C_Receptacle; USB_C_Receptacle_Amphenol_12401861XX12A
J3: Conn_02x16_Odd_Even; PinHeader_2x16_P2.54mm_Vertical
N1: Housing; Enclosure-Gloxinia2_lr

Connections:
/CC11: J1.A5 (CC1), J3.5
/CC12: J2.A5 (CC1), J3.21
/CC21: J1.B5 (CC2), J3.10
/CC22: J2.B5 (CC2), J3.28
/D+1: J1.A6 (D+), J1.B6 (D+), J3.7
/D+2: J2.A6 (D+), J2.B6 (D+), J3.23
/D-1: J1.A7 (D-), J1.B7 (D-), J3.9
/D-2: J2.A7 (D-), J2.B7 (D-), J3.25
/RX1+1: J1.B11 (RX1+), J3.4
/RX1+2: J2.B11 (RX1+), J3.22
/RX1-1: J1.B10 (RX1-), J3.6
/RX1-2: J2.B10 (RX1-), J3.24
/RX2+1: J1.A11 (RX2+), J3.15
/RX2+2: J2.A11 (RX2+), J3.31
/RX2-1: J1.A10 (RX2-), J3.13
/RX2-2: J2.A10 (RX2-), J3.29
/SBU11: J1.A8 (SBU1), J3.11
/SBU12: J2.A8 (SBU1), J3.27
/SBU21: J1.B8 (SBU2), J3.8
/SBU22: J2.B8 (SBU2), J3.26
/TX1+1: J1.A2 (TX1+), J3.1
/TX1+2: J2.A2 (TX1+), J3.17
/TX1-1: J1.A3 (TX1-), J3.3
/TX1-2: J2.A3 (TX1-), J3.19
/TX2+1: J1.B2 (TX2+), J3.14
/TX2+2: J2.B2 (TX2+), J3.32
/TX2-1: J1.B3 (TX2-), J3.12
/TX2-2: J2.B3 (TX2-), J3.30
/VBUS1: J1.A4 (VBUS), J1.A9 (VBUS), J1.B4 (VBUS), J1.B9 (VBUS), J3.2
/VBUS2: J2.A4 (VBUS), J2.A9 (VBUS), J2.B4 (VBUS), J2.B9 (VBUS), J3.20
GND: J1.A1 (GND), J1.A12 (GND), J1.B1 (GND), J1.B12 (GND), J1.S1 (SHIELD), J2.A1 (GND), J2.A12 (GND), J2.B1 (GND), J2.B12 (GND), J2.S1 (SHIELD), J3.16, J3.18
